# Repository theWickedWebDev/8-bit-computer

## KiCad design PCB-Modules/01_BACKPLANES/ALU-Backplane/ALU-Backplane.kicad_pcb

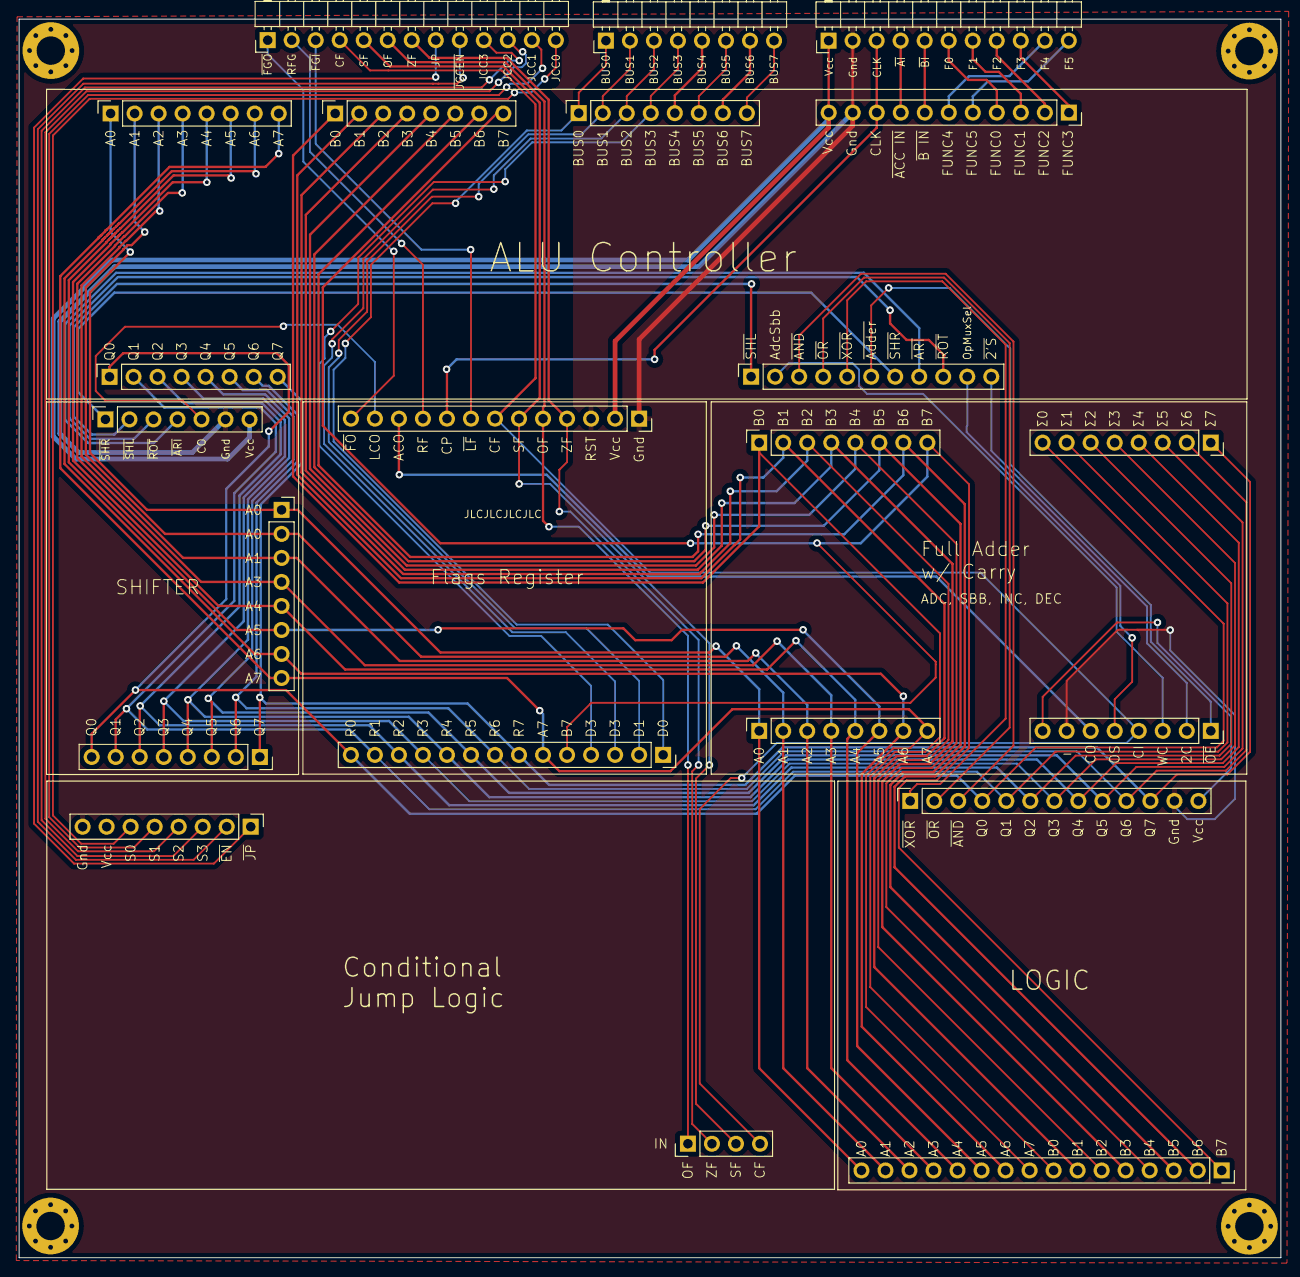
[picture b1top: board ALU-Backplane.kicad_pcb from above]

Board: 2 copper layers, 133.4 x 131.0 mm, 22 parts (0 on the bottom side), 69 nets.

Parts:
J1, J2, J5, J6, J7, J8, J22, J23, J24, J25: Conn_01x08; PinSocket_1x08_P2.54mm_Vertical
J3, J10: Conn_01x13; PinSocket_1x13_P2.54mm_Vertical
J4: Conn_01x14; PinSocket_1x14_P2.54mm_Vertical
J9: Conn_01x16; PinSocket_1x16_P2.54mm_Vertical
J11: Conn_01x08; PinHeader_1x08_P2.54mm_Vertical
J12: Conn_01x04; PinHeader_1x04_P2.54mm_Vertical
J18: Conn_01x13; PinHeader_1x13_P2.54mm_Horizontal
J19: Conn_01x07; PinSocket_1x07_P2.54mm_Vertical
J20: Conn_01x12; PinSocket_1x11_P2.54mm_Vertical
J21: Conn_01x11; PinSocket_1x11_P2.54mm_Vertical
J26: Conn_01x12; PinHeader_1x11_P2.54mm_Horizontal
J27: Conn_01x08; PinHeader_1x08_P2.54mm_Horizontal

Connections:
A0: J1.1, J8.1, J9.16, J24.1
A1: J1.2, J8.2, J9.15, J24.2
A2: J1.3, J8.3, J9.14, J24.3
A3: J1.4, J8.4, J9.13, J24.4
A4: J1.5, J8.5, J9.12, J24.5
A5: J1.6, J8.6, J9.11, J24.6
A6: J1.7, J8.7, J9.10, J24.7
A7: J1.8, J4.6, J8.8, J9.9, J24.8
ACO: J3.11, J7.6
ADC_SBB: J7.3, J21.2
ADDER_OUT: J7.1, J21.6
ALU_FUNC_0: J20.4, J26.6
ALU_FUNC_1: J20.3, J26.7
ALU_FUNC_2: J20.2, J26.8
ALU_FUNC_3: J20.1, J26.9
ALU_FUNC_4: J20.6, J26.10
ALU_FUNC_5: J20.5, J26.11
B0: J5.1, J9.8, J25.1
B1: J5.2, J9.7, J25.2
B2: J5.3, J9.6, J25.3
B3: J5.4, J9.5, J25.4
B4: J5.5, J9.4, J25.5
B5: J5.6, J9.3, J25.6
B6: J5.7, J9.2, J25.7
B7: J4.5, J5.8, J9.1, J25.8
BUS0: J4.1, J22.1, J27.1
BUS1: J4.2, J22.2, J27.2
BUS2: J4.3, J22.3, J27.3
BUS3: J4.4, J22.4, J27.4
BUS4: J22.5, J27.5
BUS5: J22.6, J27.6
BUS6: J22.7, J27.7
BUS7: J22.8, J27.8
CF: J3.7, J7.4, J12.4, J18.4
CLOCK: J3.9, J20.9, J26.3
GND: J3.1, J3.3, J7.7, J10.12, J11.8, J19.6, J20.10, J26.2
JCC_ADR0: J11.6, J18.13
JCC_ADR1: J11.5, J18.12
JCC_ADR2: J11.4, J18.11
JCC_ADR3: J11.3, J18.10
JCC_EN: J11.2, J18.9
JCC_LD_PC_COND: J11.1, J18.8
OF: J3.5, J12.1, J18.6
OP_MUX_SELECT: J7.5, J21.10
Q0: J2.8, J4.14, J6.8, J10.4, J23.1
Q1: J2.7, J4.13, J6.7, J10.5, J23.2
Q2: J2.6, J4.12, J6.6, J10.6, J23.3
Q3: J2.5, J4.11, J6.5, J10.7, J23.4
Q4: J2.4, J4.10, J6.4, J10.8, J23.5
Q5: J2.3, J4.9, J6.3, J10.9, J23.6
Q6: J2.2, J4.8, J6.2, J10.10, J23.7
Q7: J2.1, J4.7, J6.1, J10.11, J23.8
RESTORE_FLAGS: J3.10, J18.2
SF: J3.6, J12.3, J18.5
SHIFTER_CO: J3.12, J19.5
TWOS_COMP: J7.2, J21.11
VCC: J3.2, J7.8, J10.13, J11.7, J19.7, J20.11, J26.1
ZF: J3.4, J12.2, J18.7
~AND: J10.3, J21.3
~FLAGS_OUT: J3.13, J18.1
~LATCH_ACCUMULATOR: J20.8, J26.4
~LATCH_B: J20.7, J26.5
~LATCH_FLAGS: J3.8, J18.3
~OR: J10.2, J21.4
~SHIFTER_ARI: J19.4, J21.8
~SHIFTER_ROT: J19.3, J21.9
~SHIFTER_SHL: J19.2, J21.1
~SHIFTER_SHR: J19.1, J21.7
~XOR: J10.1, J21.5

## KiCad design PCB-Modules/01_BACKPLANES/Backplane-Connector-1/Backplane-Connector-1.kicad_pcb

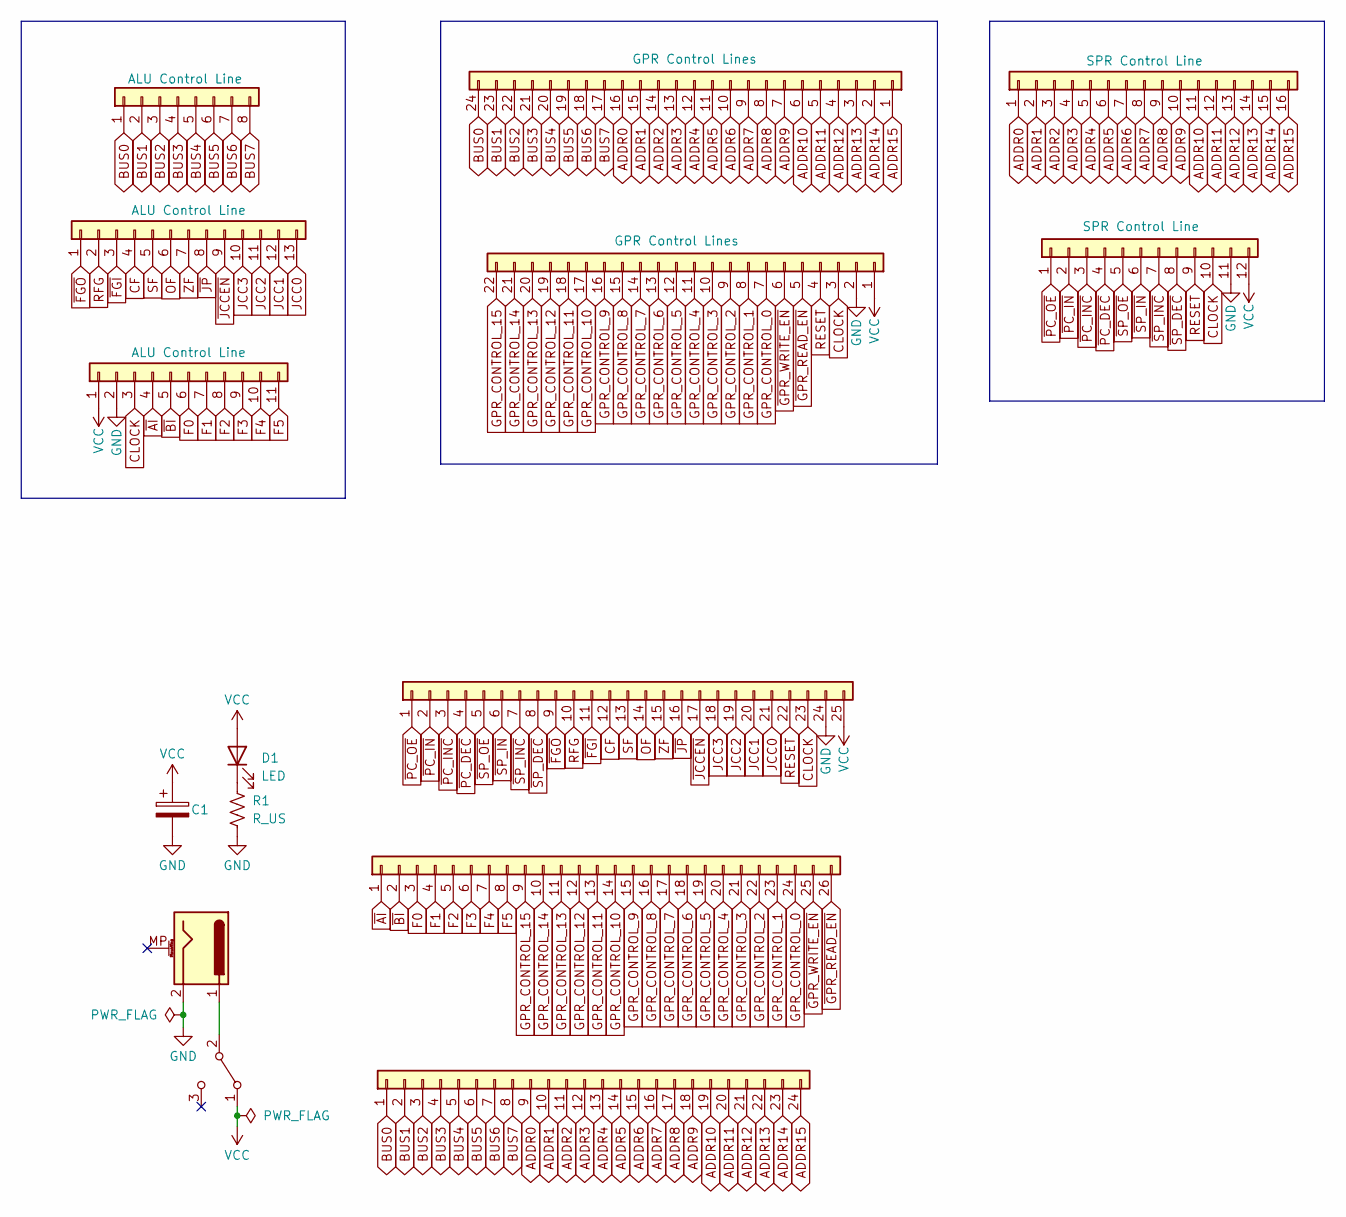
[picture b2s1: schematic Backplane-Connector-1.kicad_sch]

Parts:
C1: C_Polarized; CP_Elec_5x5.9
D1: LED; LED_0805_2012Metric
J1: Conn_01x08; PinHeader_1x08_P2.54mm_Vertical
J2: Conn_01x13; PinHeader_1x13_P2.54mm_Vertical
J3: Conn_01x11; PinHeader_1x11_P2.54mm_Vertical
J4, J8: Conn_01x24; PinHeader_1x24_P2.54mm_Vertical
J5: Conn_01x22; PinHeader_1x22_P2.54mm_Vertical
J6: Conn_01x12; PinHeader_1x12_P2.54mm_Vertical
J7: Conn_01x16; PinHeader_1x16_P2.54mm_Vertical
J9: Barrel_Jack_MountingPin; BarrelJack_Horizontal
J10: Conn_01x26; PinHeader_1x26_P2.54mm_Vertical
J11: Conn_01x25; PinHeader_1x25_P2.54mm_Vertical
R1: R_US; R_0805_2012Metric
SW1: SW_DPDT_x2; PinHeader_1x03_P2.54mm_Vertical

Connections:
ADDR0: J4.16, J7.1, J8.9
ADDR1: J4.15, J7.2, J8.10
ADDR2: J4.14, J7.3, J8.11
ADDR3: J4.13, J7.4, J8.12
ADDR4: J4.12, J7.5, J8.13
ADDR5: J4.11, J7.6, J8.14
ADDR6: J4.10, J7.7, J8.15
ADDR7: J4.9, J7.8, J8.16
ADDR8: J4.8, J7.9, J8.17
ADDR9: J4.7, J7.10, J8.18
ADDR10: J4.6, J7.11, J8.19
ADDR11: J4.5, J7.12, J8.20
ADDR12: J4.4, J7.13, J8.21
ADDR13: J4.3, J7.14, J8.22
ADDR14: J4.2, J7.15, J8.23
ADDR15: J4.1, J7.16, J8.24
BUS0: J1.1, J4.24, J8.1
BUS1: J1.2, J4.23, J8.2
BUS2: J1.3, J4.22, J8.3
BUS3: J1.4, J4.21, J8.4
BUS4: J1.5, J4.20, J8.5
BUS5: J1.6, J4.19, J8.6
BUS6: J1.7, J4.18, J8.7
BUS7: J1.8, J4.17, J8.8
CF: J2.4, J11.12
CLOCK: J3.3, J5.3, J6.10, J11.23
F0: J3.6, J10.3
F1: J3.7, J10.4
F2: J3.8, J10.5
F3: J3.9, J10.6
F4: J3.10, J10.7
F5: J3.11, J10.8
GND: C1.2, J3.2, J5.2, J6.11, J9.2, J11.24, R1.2
GPR_CONTROL_0: J5.7, J10.24
GPR_CONTROL_1: J5.8, J10.23
GPR_CONTROL_2: J5.9, J10.22
GPR_CONTROL_3: J5.10, J10.21
GPR_CONTROL_4: J5.11, J10.20
GPR_CONTROL_5: J5.12, J10.19
GPR_CONTROL_6: J5.13, J10.18
GPR_CONTROL_7: J5.14, J10.17
GPR_CONTROL_8: J5.15, J10.16
GPR_CONTROL_9: J5.16, J10.15
GPR_CONTROL_10: J5.17, J10.14
GPR_CONTROL_11: J5.18, J10.13
GPR_CONTROL_12: J5.19, J10.12
GPR_CONTROL_13: J5.20, J10.11
GPR_CONTROL_14: J5.21, J10.10
GPR_CONTROL_15: J5.22, J10.9
JCC0: J2.13, J11.21
JCC1: J2.12, J11.20
JCC2: J2.11, J11.19
JCC3: J2.10, J11.18
unnamed: D1.1 (K), R1.1
unnamed: J9.1, SW1.2 (B)
OF: J2.6, J11.14
RESET: J5.4, J6.9, J11.22
RFG: J2.2, J11.10
SF: J2.5, J11.13
VCC: C1.1, D1.2 (A), J3.1, J5.1, J6.12, J11.25, SW1.1 (A)
ZF: J2.7, J11.15
~AI: J3.4, J10.1
~BI: J3.5, J10.2
~FGI: J2.3, J11.11
~FGO: J2.1, J11.9
~GPR_READ_EN: J5.5, J10.26
~GPR_WRITE_EN: J5.6, J10.25
~JCCEN: J2.9, J11.17
~JP: J2.8, J11.16
~PC_DEC: J6.4, J11.4
~PC_INC: J6.3, J11.3
~PC_IN: J6.2, J11.2
~PC_OE: J6.1, J11.1
~SP_DEC: J6.8, J11.8
~SP_INC: J6.7, J11.7
~SP_IN: J6.6, J11.6
~SP_OE: J6.5, J11.5

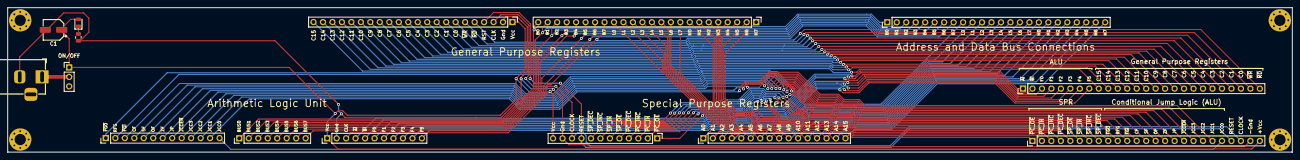
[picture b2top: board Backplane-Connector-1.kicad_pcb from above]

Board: 2 copper layers, 344.4 x 38.7 mm, 15 parts (0 on the bottom side), 77 nets.

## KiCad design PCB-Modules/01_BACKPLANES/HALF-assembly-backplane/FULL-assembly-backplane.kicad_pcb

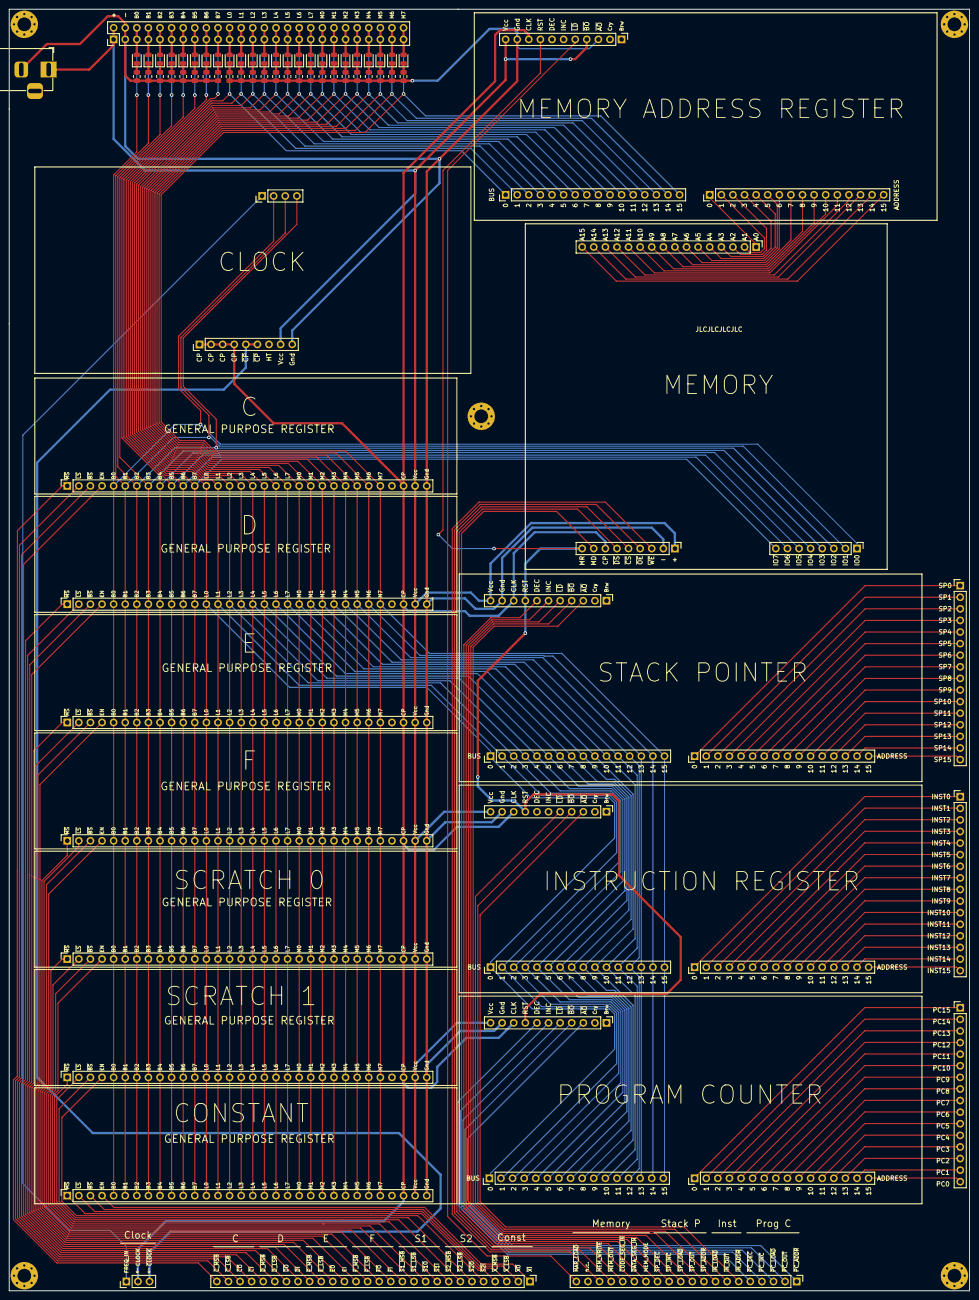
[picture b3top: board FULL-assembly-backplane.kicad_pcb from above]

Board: 2 copper layers, 210.3 x 280.7 mm, 80 parts (0 on the bottom side), 165 nets.

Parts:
D1, D2, D3, D4, D5, D6, D7, D8, D9, D10, D11, D12, D13, D14, D15, D16, D17, D18, D19, D20, D21, D22, D23, D24: LED; LED_0805_2012Metric
J1: Conn_01x28; PinHeader_1x28_P2.54mm_Vertical
J2: Conn_01x20; PinHeader_1x20_P2.54mm_Vertical
J3: Conn_01x08; PinHeader_1x08_P2.54mm_Vertical
J4, J5: Conn_01x09; PinHeader_1x09_P2.54mm_Vertical
J6, J7, J8, J9, J10, J11, J12, J13, J14, J15, J16, J17: Conn_01x16; PinHeader_1x16_P2.54mm_Vertical
J18, J19, J20, J21: Conn_01x11; PinHeader_1x11_P2.54mm_Vertical
J22: Conn_01x04; PinHeader_1x04_P2.54mm_Vertical
J24: Conn_01x03; PinHeader_1x03_P2.54mm_Vertical
J25, J26, J32, J33, J34, J35, J36: Conn_01x32; PinSocket_1x32_P2.54mm_Vertical
J37: Conn_01x26; PinHeader_2x26_P2.54mm_Vertical
J43: Barrel_Jack; BarrelJack_Horizontal
R1, R2, R3, R4, R5, R6, R7, R8, R9, R10, R11, R12, R13, R14, R15, R16, R17, R18, R19, R20, R21, R22, R23, R24: R_US; R_0805_2012Metric

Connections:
/IN_B0: J9.1, J11.1
/IN_B1: J9.2, J11.2
/IN_B2: J9.3, J11.3
/IN_B3: J9.4, J11.4
/IN_B4: J9.5, J11.5
/IN_B5: J9.6, J11.6
/IN_B6: J9.7, J11.7
/IN_B7: J9.8, J11.8
/IN_B8: J9.9, J11.9
/IN_B9: J9.10, J11.10
/IN_B10: J9.11, J11.11
/IN_B11: J9.12, J11.12
/IN_B12: J9.13, J11.13
/IN_B13: J9.14, J11.14
/IN_B14: J9.15, J11.15
/IN_B15: J9.16, J11.16
/MAR_B0: J15.1, J17.1
/MAR_B1: J15.2, J17.2
/MAR_B2: J15.3, J17.3
/MAR_B3: J15.4, J17.4
/MAR_B4: J15.5, J17.5
/MAR_B5: J15.6, J17.6
/MAR_B6: J15.7, J17.7
/MAR_B7: J15.8, J17.8
/MAR_B8: J15.9, J17.9
/MAR_B9: J15.10, J17.10
/MAR_B10: J15.11, J17.11
/MAR_B11: J15.12, J17.12
/MAR_B12: J15.13, J17.13
/MAR_B13: J15.14, J17.14
/MAR_B14: J15.15, J17.15
/MAR_B15: J15.16, J17.16
/PC_B0: J12.1, J14.1
/PC_B1: J12.2, J14.2
/PC_B2: J12.3, J14.3
/PC_B3: J12.4, J14.4
/PC_B4: J12.5, J14.5
/PC_B5: J12.6, J14.6
/PC_B6: J12.7, J14.7
/PC_B7: J12.8, J14.8
/PC_B8: J12.9, J14.9
/PC_B9: J12.10, J14.10
/PC_B10: J12.11, J14.11
/PC_B11: J12.12, J14.12
/PC_B12: J12.13, J14.13
/PC_B13: J12.14, J14.14
/PC_B14: J12.15, J14.15
/PC_B15: J12.16, J14.16
/SP_B0: J6.1, J8.1
/SP_B1: J6.2, J8.2
/SP_B2: J6.3, J8.3
/SP_B3: J6.4, J8.4
/SP_B4: J6.5, J8.5
/SP_B5: J6.6, J8.6
/SP_B6: J6.7, J8.7
/SP_B7: J6.8, J8.8
/SP_B8: J6.9, J8.9
/SP_B9: J6.10, J8.10
/SP_B10: J6.11, J8.11
/SP_B11: J6.12, J8.12
/SP_B12: J6.13, J8.13
/SP_B13: J6.14, J8.14
/SP_B14: J6.15, J8.15
/SP_B15: J6.16, J8.16
BUS0: D1.2, J3.1, J22.2, J25.5, J26.5, J32.5, J33.5, J34.5, J35.5, J36.5, J37.5, J37.6
BUS1: D2.2, J3.2, J22.3, J25.6, J26.6, J32.6, J33.6, J34.6, J35.6, J36.6, J37.7, J37.8
BUS2: D3.2, J3.3, J22.4, J25.7, J26.7, J32.7, J33.7, J34.7, J35.7, J36.7, J37.9, J37.10
BUS3: D4.2, J3.4, J25.8, J26.8, J32.8, J33.8, J34.8, J35.8, J36.8, J37.11, J37.12
BUS4: D5.2, J3.5, J25.9, J26.9, J32.9, J33.9, J34.9, J35.9, J36.9, J37.13, J37.14
BUS5: D6.2, J3.6, J25.10, J26.10, J32.10, J33.10, J34.10, J35.10, J36.10, J37.15, J37.16
BUS6: D7.2, J3.7, J25.11, J26.11, J32.11, J33.11, J34.11, J35.11, J36.11, J37.17, J37.18
BUS7: D8.2, J3.8, J25.12, J26.12, J32.12, J33.12, J34.12, J35.12, J36.12, J37.19, J37.20
CLOCK: J4.7, J5.1, J5.2, J5.3, J5.4, J18.9, J19.9, J20.9, J21.9, J24.2, J25.30, J26.30, J32.30, J33.30, J34.30, J35.30, J36.30
FREQ_IN: J22.1, J24.1
GND: J4.2, J5.9, J18.10, J19.10, J20.3, J20.10, J21.10, J25.32, J26.32, J32.32, J33.32, J34.32, J35.32, J36.32, J37.3, J37.4, J43.2, R1.2, R2.2, R3.2, R4.2, R5.2, R6.2, R7.2, R8.2, R9.2, R10.2, R11.2, R12.2, R13.2, R14.2, R15.2, R16.2, R17.2, R18.2, R19.2, R20.2, R21.2, R22.2, R23.2, R24.2
I_C: J1.25, J32.4
I_CONST: J1.1, J26.4
I_D: J1.21, J33.4
I_E: J1.17, J34.4
I_F: J1.13, J35.4
I_SCR_0: J1.9, J36.4
I_SCR_1: J1.5, J25.4
L0: D9.2, J7.1, J10.1, J13.1, J16.1, J25.13, J26.13, J32.13, J33.13, J34.13, J35.13, J36.13, J37.21, J37.22
L1: D10.2, J7.2, J10.2, J13.2, J16.2, J25.14, J26.14, J32.14, J33.14, J34.14, J35.14, J36.14, J37.23, J37.24
L2: D11.2, J7.3, J10.3, J13.3, J16.3, J25.15, J26.15, J32.15, J33.15, J34.15, J35.15, J36.15, J37.25, J37.26
L3: D12.2, J7.4, J10.4, J13.4, J16.4, J25.16, J26.16, J32.16, J33.16, J34.16, J35.16, J36.16, J37.27, J37.28
L4: D13.2, J7.5, J10.5, J13.5, J16.5, J25.17, J26.17, J32.17, J33.17, J34.17, J35.17, J36.17, J37.29, J37.30
L5: D14.2, J7.6, J10.6, J13.6, J16.6, J25.18, J26.18, J32.18, J33.18, J34.18, J35.18, J36.18, J37.31, J37.32
L6: D15.2, J7.7, J10.7, J13.7, J16.7, J25.19, J26.19, J32.19, J33.19, J34.19, J35.19, J36.19, J37.33, J37.34
L7: D16.2, J7.8, J10.8, J13.8, J16.8, J25.20, J26.20, J32.20, J33.20, J34.20, J35.20, J36.20, J37.35, J37.36
LSB_C: J1.27, J32.2
LSB_CONST: J1.3, J26.2
LSB_D: J1.23, J33.2
LSB_E: J1.19, J34.2
LSB_F: J1.15, J35.2
LSB_SCR_0: J1.11, J36.2
LSB_SCR_1: J1.7, J25.2
M0: D17.2, J7.9, J10.9, J13.9, J16.9, J25.21, J26.21, J32.21, J33.21, J34.21, J35.21, J36.21, J37.37, J37.38
M1: D18.2, J7.10, J10.10, J13.10, J16.10, J25.22, J26.22, J32.22, J33.22, J34.22, J35.22, J36.22, J37.39, J37.40
M2: D19.2, J7.11, J10.11, J13.11, J16.11, J25.23, J26.23, J32.23, J33.23, J34.23, J35.23, J36.23, J37.41, J37.42
M3: D20.2, J7.12, J10.12, J13.12, J16.12, J25.24, J26.24, J32.24, J33.24, J34.24, J35.24, J36.24, J37.43, J37.44
M4: D21.2, J7.13, J10.13, J13.13, J16.13, J25.25, J26.25, J32.25, J33.25, J34.25, J35.25, J36.25, J37.45, J37.46
M5: D22.2, J7.14, J10.14, J13.14, J16.14, J25.26, J26.26, J32.26, J33.26, J34.26, J35.26, J36.26, J37.47, J37.48
M6: D23.2, J7.15, J10.15, J13.15, J16.15, J25.27, J26.27, J32.27, J33.27, J34.27, J35.27, J36.27, J37.49, J37.50
M7: D24.2, J7.16, J10.16, J13.16, J16.16, J25.28, J26.28, J32.28, J33.28, J34.28, J35.28, J36.28, J37.51, J37.52
MODE: J2.14, J4.8
MSB_C: J1.28, J32.1
MSB_CONST: J1.4, J26.1
MSB_D: J1.24, J33.1
MSB_E: J1.20, J34.1
MSB_F: J1.16, J35.1
MSB_SCR_0: J1.12, J36.1
MSB_SCR_1: J1.8, J25.1
unnamed: D1.1, R1.1
unnamed: D2.1, R2.1
unnamed: D3.1, R3.1
unnamed: D4.1, R4.1
unnamed: D5.1, R5.1
unnamed: D6.1, R6.1
unnamed: D7.1, R7.1
unnamed: D8.1, R8.1
unnamed: D9.1, R9.1
unnamed: D10.1, R10.1
unnamed: D11.1, R11.1
unnamed: D12.1, R12.1
unnamed: D13.1, R13.1
unnamed: D14.1, R14.1
unnamed: D15.1, R15.1
unnamed: D16.1, R16.1
unnamed: D17.1, R17.1
unnamed: D18.1, R18.1
unnamed: D19.1, R19.1
unnamed: D20.1, R20.1
unnamed: D21.1, R21.1
unnamed: D22.1, R22.1
unnamed: D23.1, R23.1
unnamed: D24.1, R24.1
O_C: J1.26, J32.3
O_CONST: J1.2, J26.3
O_D: J1.22, J33.3
O_E: J1.18, J34.3
O_F: J1.14, J35.3
O_SCR_0: J1.10, J36.3
O_SCR_1: J1.6, J25.3
PC_DEC: J2.5, J21.7
PC_INC: J2.4, J21.6
RESET: J4.9, J18.8, J19.8, J20.8, J21.8
SP_DEC: J2.13, J18.7
SP_INC: J2.12, J18.6
VCC: J4.1, J5.8, J18.11, J19.11, J20.4, J20.11, J21.11, J25.31, J26.31, J32.31, J33.31, J34.31, J35.31, J36.31, J37.1, J37.2, J43.1
~CLOCK: J5.5, J5.6, J24.3
~CS: J2.16, J4.5
~DS: J2.15, J4.6
~IN_ADDR: J2.6, J19.3
~IN_BO: J2.7, J19.4
~IN_LD: J2.8, J19.5
~LD_STACK_P: J2.11, J18.5
~MAR_LD: J2.20, J20.5
~OE: J2.17, J4.4
~PC_ADDR: J2.1, J21.3
~PC_BO: J2.2, J21.4
~PC_LD: J2.3, J21.5
~SP_ADDR: J2.9, J18.3
~SP_BO: J2.10, J18.4
~WE: J2.18, J4.3

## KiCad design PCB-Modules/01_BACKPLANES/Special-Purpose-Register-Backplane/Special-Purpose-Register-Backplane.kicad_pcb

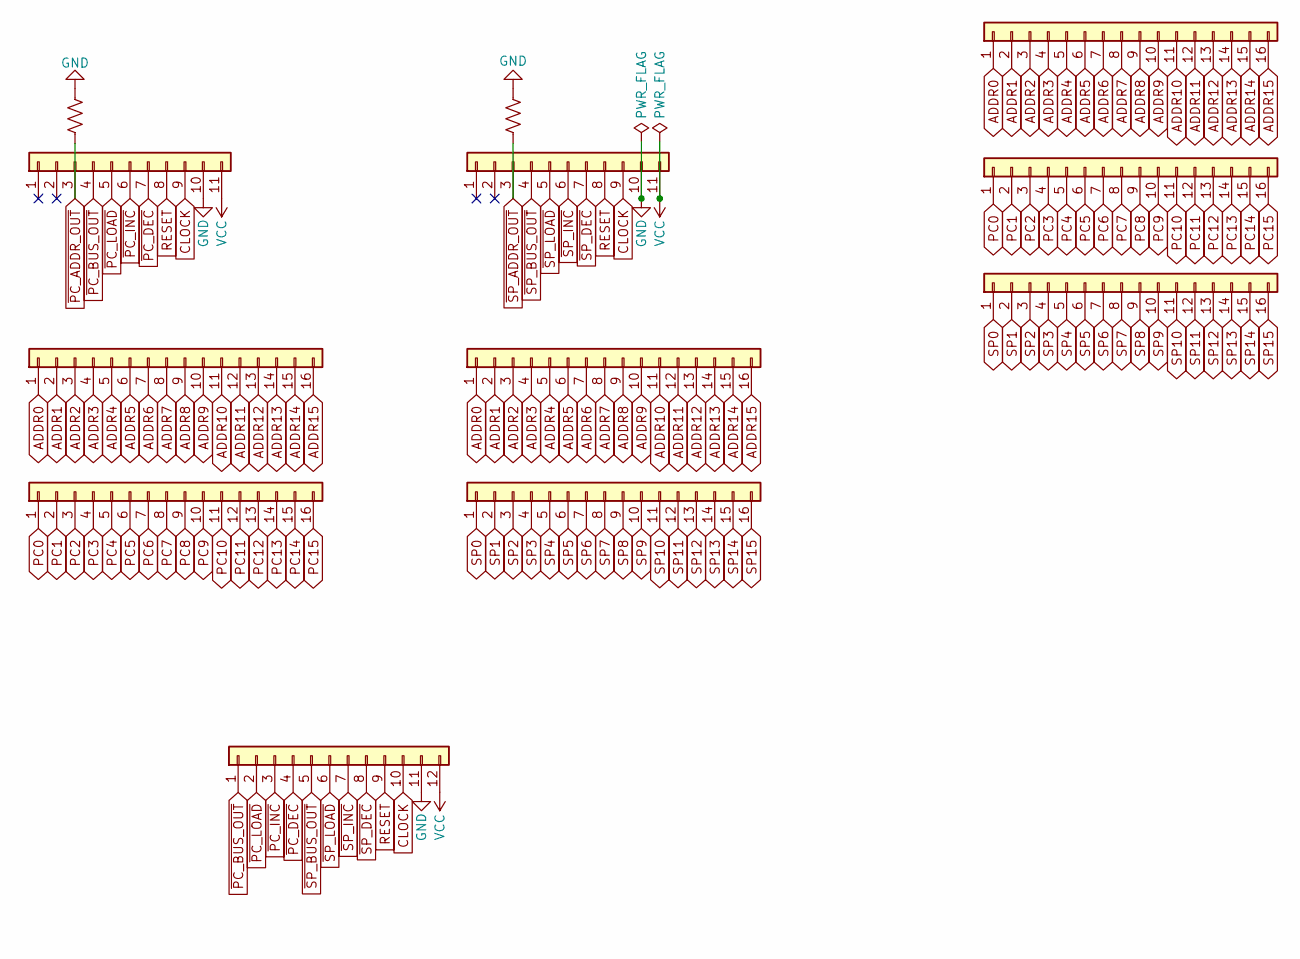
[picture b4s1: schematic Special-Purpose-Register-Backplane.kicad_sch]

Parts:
J1, J4: Conn_01x11; PinHeader_1x11_P2.54mm_Vertical
J2, J3, J5, J6, J8, J9, J10: Conn_01x16; PinHeader_1x16_P2.54mm_Vertical
J7: Conn_01x12; PinHeader_1x12_P2.54mm_Vertical
R1, R2: R_US; R_0805_2012Metric

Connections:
ADDR0: J2.1, J5.1, J8.1
ADDR1: J2.2, J5.2, J8.2
ADDR2: J2.3, J5.3, J8.3
ADDR3: J2.4, J5.4, J8.4
ADDR4: J2.5, J5.5, J8.5
ADDR5: J2.6, J5.6, J8.6
ADDR6: J2.7, J5.7, J8.7
ADDR7: J2.8, J5.8, J8.8
ADDR8: J2.9, J5.9, J8.9
ADDR9: J2.10, J5.10, J8.10
ADDR10: J2.11, J5.11, J8.11
ADDR11: J2.12, J5.12, J8.12
ADDR12: J2.13, J5.13, J8.13
ADDR13: J2.14, J5.14, J8.14
ADDR14: J2.15, J5.15, J8.15
ADDR15: J2.16, J5.16, J8.16
CLOCK: J1.9, J4.9, J7.10
GND: J1.10, J4.10, J7.11, R1.1, R2.1
PC0: J3.1, J9.1
PC1: J3.2, J9.2
PC2: J3.3, J9.3
PC3: J3.4, J9.4
PC4: J3.5, J9.5
PC5: J3.6, J9.6
PC6: J3.7, J9.7
PC7: J3.8, J9.8
PC8: J3.9, J9.9
PC9: J3.10, J9.10
PC10: J3.11, J9.11
PC11: J3.12, J9.12
PC12: J3.13, J9.13
PC13: J3.14, J9.14
PC14: J3.15, J9.15
PC15: J3.16, J9.16
RESET: J1.8, J4.8, J7.9
SP0: J6.1, J10.1
SP1: J6.2, J10.2
SP2: J6.3, J10.3
SP3: J6.4, J10.4
SP4: J6.5, J10.5
SP5: J6.6, J10.6
SP6: J6.7, J10.7
SP7: J6.8, J10.8
SP8: J6.9, J10.9
SP9: J6.10, J10.10
SP10: J6.11, J10.11
SP11: J6.12, J10.12
SP12: J6.13, J10.13
SP13: J6.14, J10.14
SP14: J6.15, J10.15
SP15: J6.16, J10.16
VCC: J1.11, J4.11, J7.12
~PC_ADDR_OUT: J1.3, R1.2
~PC_BUS_OUT: J1.4, J7.1
~PC_DEC: J1.7, J7.4
~PC_INC: J1.6, J7.3
~PC_LOAD: J1.5, J7.2
~SP_ADDR_OUT: J4.3, R2.2
~SP_BUS_OUT: J4.4, J7.5
~SP_DEC: J4.7, J7.8
~SP_INC: J4.6, J7.7
~SP_LOAD: J4.5, J7.6

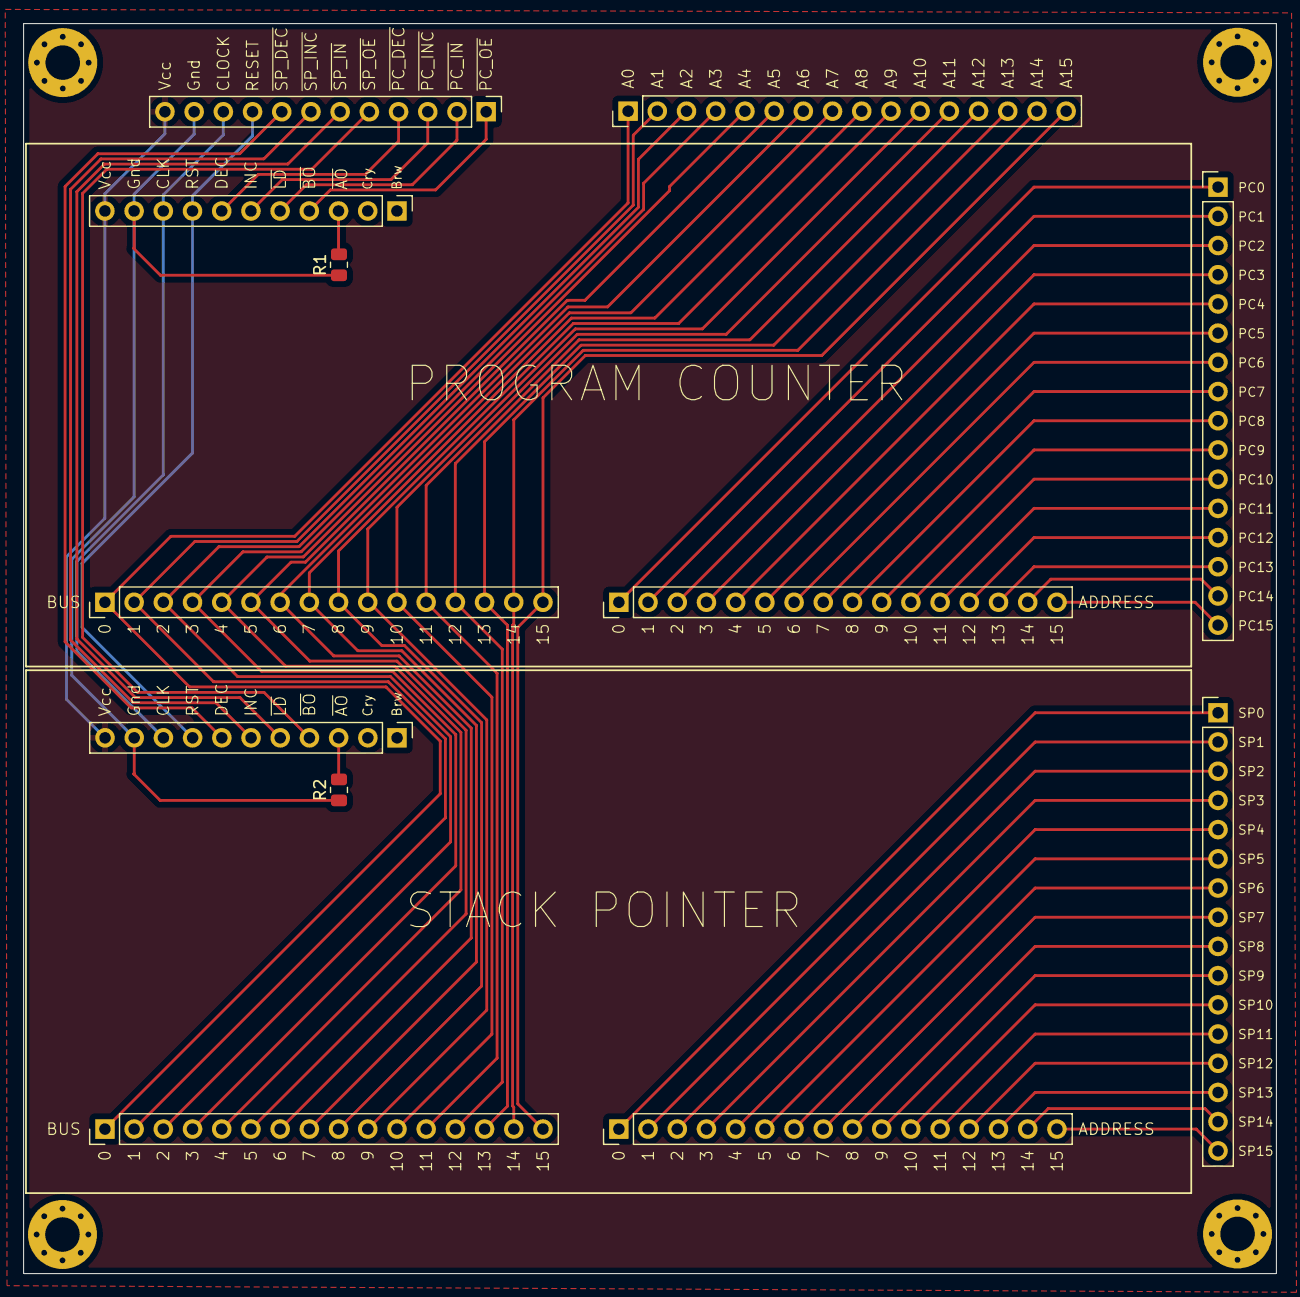
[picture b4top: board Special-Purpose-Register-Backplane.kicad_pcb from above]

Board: 2 copper layers, 109.0 x 108.7 mm, 12 parts (0 on the bottom side), 62 nets.

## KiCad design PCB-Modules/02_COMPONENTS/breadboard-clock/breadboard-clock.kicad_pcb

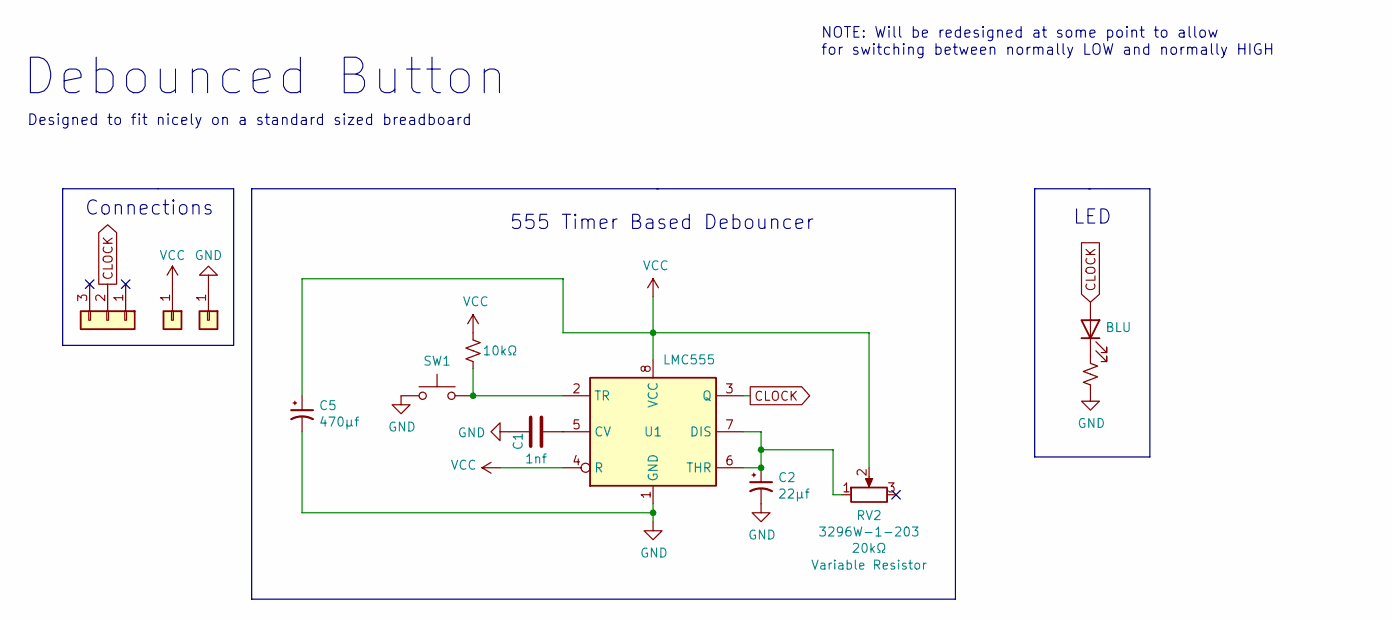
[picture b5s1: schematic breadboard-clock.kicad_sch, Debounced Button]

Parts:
C1: 0402B102K500NT; C_0402_1005Metric; JLCPCB C1523
C2: CS1V220M-CRE54; CP_Elec_6.3x5.4; JLCPCB C116086
C5: CS1A471M-CRE77; CP_Elec_6.3x7.7; JLCPCB C116423
D12: 19-217/BHC-ZL1M2RY/3T; LED_0603_1608Metric; JLCPCB C72041
J2: Conn_01x03; PinHeader_1x03_P2.54mm_Vertical
J3, J4: Conn_01x01; PinHeader_1x01_P2.54mm_Vertical
R1: 0402WGF1002TCE; R_0402_1005Metric; JLCPCB C25744
R12: 0402WGF1001TCE; R_0402_1005Metric; JLCPCB C11702
RV2: 3296W-1-203; Potentiometer_Bourns_3266Y_Vertical; JLCPCB C118936
SW1: sw-push; SW_PUSH_6mm
U1: LMC555CMX/NOPB; SOIC-8_3.9x4.9mm_P1.27mm; JLCPCB C90760

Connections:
CLOCK: D12.2 (A), J2.2, U1.3 (Q)
GND: C1.2, C2.2, C5.2, J4.1, R12.2, SW1.1, U1.1 (GND)
unnamed: C1.1, U1.5 (CV)
unnamed: C2.1, RV2.1, U1.6 (THR), U1.7 (DIS)
unnamed: D12.1 (K), R12.1
unnamed: R1.2, SW1.2, U1.2 (TR)
VCC: C5.1, J3.1, R1.1, RV2.2, U1.4 (R), U1.8 (VCC)

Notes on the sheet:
555 Timer Based Debouncer
LED
Connections
Debounced Button
Designed to fit nicely on a standard sized breadboard
NOTE: Will be redesigned at some point to allow for switching between normally LOW and normally HIGH

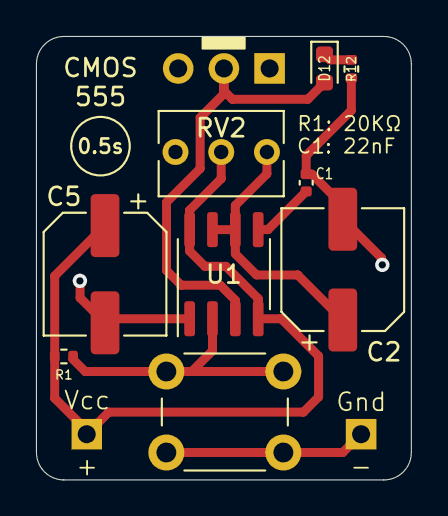
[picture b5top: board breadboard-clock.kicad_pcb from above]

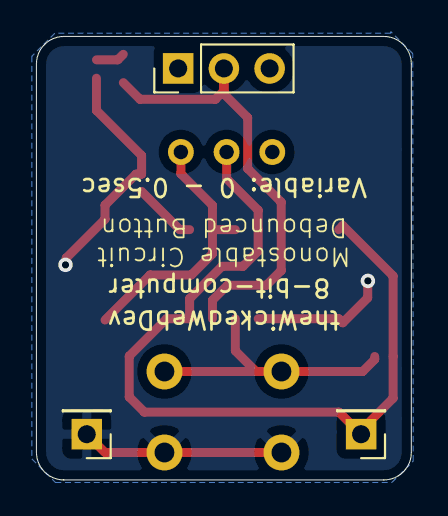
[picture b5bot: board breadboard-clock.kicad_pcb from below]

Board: 2 copper layers, 20.8 x 24.6 mm, 12 parts (3 on the bottom side), 7 nets.

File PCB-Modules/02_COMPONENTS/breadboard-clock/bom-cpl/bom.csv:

Reference, Quantity, Value, Footprint, Datasheet, Description, JLCPCB, LCSC, LCSC Part Number, R, C, Color
C1 ,1,"0402B102K500NT","Capacitor_SMD:C_0402_1005Metric","https://datasheet.lcsc.com/lcsc/1809291524_FH-Guangdong-Feng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","X7R 1nF ±10% 50V 0402 Multilayer Ceramic Capacitors MLCC - SMD/SMT ROHS","C1523","C1523","C1523","","1nf",""
C2 ,1,"CS1V220M-CRE54","Capacitor_SMD:CP_Elec_6.3x5.4","https://datasheet.lcsc.com/lcsc/1811082138_ST-Semtech-CS1V22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","- - 1000hrs 105℃ 35V 22uF 6.3mm ±20% -40℃~+105℃ 5.4mm SMD,6.3x5.4mm Aluminum Electrolytic Capacitors - SMD ROHS","C116086","C116086","C116086","","22µf",""
C5 ,1,"CS1A471M-CRE77","Capacitor_SMD:CP_Elec_6.3x7.7","https://datasheet.lcsc.com/lcsc/1811061025_ST-Semtech-CS1A47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","- - 470uF 6.3mm 7.7mm 2000hrs 105℃ ±20% 10V -40℃~+105℃ SMD,6.3x7.7mm Aluminum Electrolytic Capacitors - SMD ROHS","C116423","C116423","C116423","","470µf",""
D12 ,1,"19-217/BHC-ZL1M2RY/3T","LED_SMD:LED_0603_1608Metric","https://datasheet.lcsc.com/lcsc/1811101510_Everlight-Elec-19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","","C72041","C72041","C72041","","","BLU"
J2 ,1,"Conn_01x03","Connector_PinHeader_2.54mm:PinHeader_1x03_P2.54mm_Vertical","~"
J3 J4 ,2,"Conn_01x01","Connector_PinHeader_2.54mm:PinHeader_1x01_P2.54mm_Vertical","~"
R1 ,1,"0402WGF1002TCE","Resistor_SMD:R_0402_1005Metric","https://datasheet.lcsc.com/lcsc/1809301717_UNI-ROYAL-Uniroya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","1/16W ±1% ±100ppm/℃ 10kΩ 0402 Chip Resistor - Surface Mount ROHS","C25744","C25744","C25744","10kΩ","",""
R12 ,1,"0402WGF1001TCE","Resistor_SMD:R_0402_1005Metric","https://datasheet.lcsc.com/lcsc/1811132311_UNI-ROYAL-Uniroya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","±1% 1/16W ±100ppm/℃ 1kΩ 0402 Chip Resistor - Surface Mount ROHS","C11702","C11702","C11702","","",""
RV2 ,1,"3296W-1-203","Potentiometer_THT:Potentiometer_Bourns_3266Y_Vertical","https://datasheet.lcsc.com/lcsc/1811011713_BOCHEN-Chengdu-Gu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","Variable Resistors 20kΩ ±10% ±250ppm/℃ 3296W Variable Resistors/Potentiometers ROHS","C118936","C118936","C118936","20kΩ","20kΩ",""
SW1 ,1,"sw-push","Button_Switch_THT:SW_PUSH_6mm",""
U1 ,1,"LMC555CMX/NOPB","Package_SO:SOIC-8_3.9x4.9mm_P1.27mm","https://datasheet.lcsc.com/lcsc/1810181624_Texas-Instruments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","SOIC-8_150mil Timer ROHS","C90760","C90760","C90760","","",""
